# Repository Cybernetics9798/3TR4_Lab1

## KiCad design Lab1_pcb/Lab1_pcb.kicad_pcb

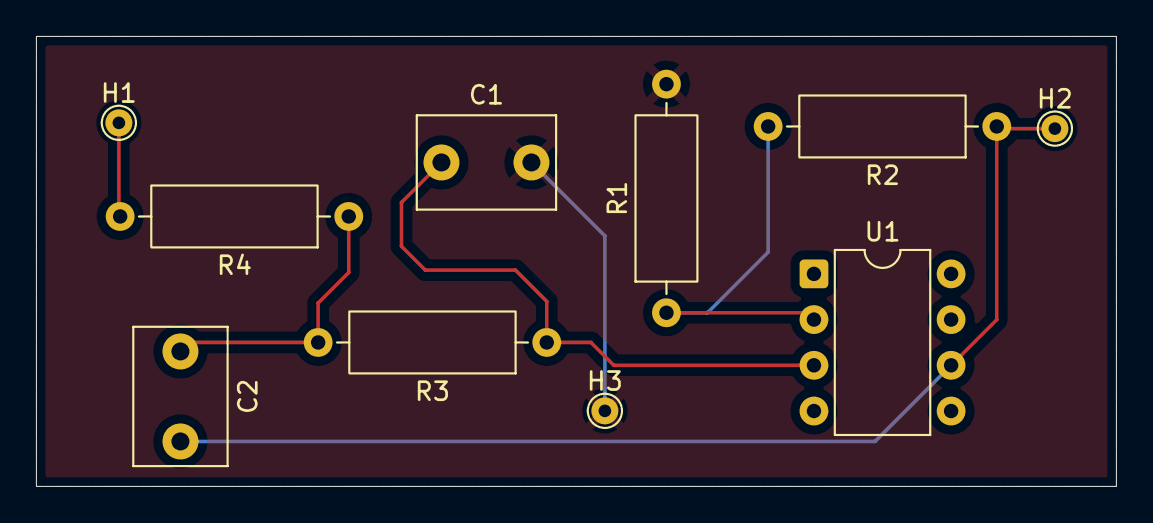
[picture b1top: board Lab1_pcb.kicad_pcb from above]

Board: 2 copper layers, 60.0 x 25.0 mm, 10 parts (0 on the bottom side), 6 nets.

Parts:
C1, C2: 0.00000001; C_Disc_D7.5mm_W5.0mm_P5.00mm
H1, H2, H3: MountingHole_Pad; TestPoint_THTPad_D1.5mm_Drill0.7mm
R1, R2, R3, R4: 2000; R_Axial_DIN0309_L9.0mm_D3.2mm_P12.70mm_Horizontal
U1: LT6238; DIP-8_W7.62mm

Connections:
GND: C1.2, H3.1, R1.2
unnamed: C2.1, R3.2, R4.1
unnamed: H1.1, R4.2
unnamed: C1.1, R3.1, U1.3 (IN+)
unnamed: R1.1, R2.2, U1.2 (IN-)
unnamed: C2.2, H2.1, R2.1, U1.6 (OUT)

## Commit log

2025-10-07 added pcb
2025-10-08 gerber update
